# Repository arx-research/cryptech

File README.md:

# CrypTech Repos

This repository is a collection of git submodules associated with the [CrypTech](https://cryptech.is) project.

To use on a fresh repository run:
`git clone --recurse-submodules -j8 https://github.com/arx-project/cryptech.git`

Or on an already cloned repo:
`git submodule update --init --recursive`

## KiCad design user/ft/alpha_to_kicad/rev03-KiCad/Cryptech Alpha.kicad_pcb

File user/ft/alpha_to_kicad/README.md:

Work-in-progress repository with output of altium2kicad conversion
of the Cryptech Alpha rev03 board.

The conversion was done using 'convert.sh', with the Altium Designer
project files from

  https://wiki.cryptech.is/browser/hardware/cad/rev03

and the altium2kicad project from

  https://github.com/thesourcerer8/altium2kicad

Current status
--------------
NOTE: The latest stable KiCAD version as of this writing is 4.0.7 - it does
NOT include necessary support for stitching vias. Install KiCAD nightly build
to work with the Cryptech Alpha PCB.

The schematics are mostly converted. A few components do not connect with their
nets (e.g. C9 and C10 on sheet rev02_01), but maybe a manual overhaul will be
needed anyways at the end of conversion. A bigger issue is that no components
get footprints associated with them in the schema, so generating a new netlist
won't work at all. The footprints exists in some form in the PCB, so we only
need to figure out how to reference them properly in the schema.

All the copper layers convert reasonably well. The challenges are mostly
around filled polygons on the various layers. A python script (fix-pcb.py)
modifies parameters to get a fairly close result.

I'm currently looking into ensuring the drill hole sizes are right, and the
non-copper layers have been largely ignored this far.

Issues
------
Two layers (Altium Gerber files CrypTech.G1 and CrypTech.G2) have fills
that I have not been able to reproduce. I targeted not missing any copper,
accepting that the KiCAD gerber fills reach more places, so add some copper
on those layers.

Drill hole sizes have not been checked. KiCAD seems to add ~0.85 mil more
clearance around vias. This needs to be double checked but I'm hoping that
we can just tolerate that.

Importing WRL files (3D models) required some hacking of the altium2kicad
tool that I haven't been able to work on upstreaming yet. Something is still
not right here, but the board does have a fair amount of component (including
the more special ones) in KiCAD 3D view.

Another hack that has not been upstreamed is loading more of the source
files, IIRC to get all component footprints properly converted.

The KiCAD board does not pass DRC checks yet. I believe part of this is
because design rule settings aren't (fully?) imported from Altium. Need
to figure out the settings used for this project, and fix all drill sizes
I think.

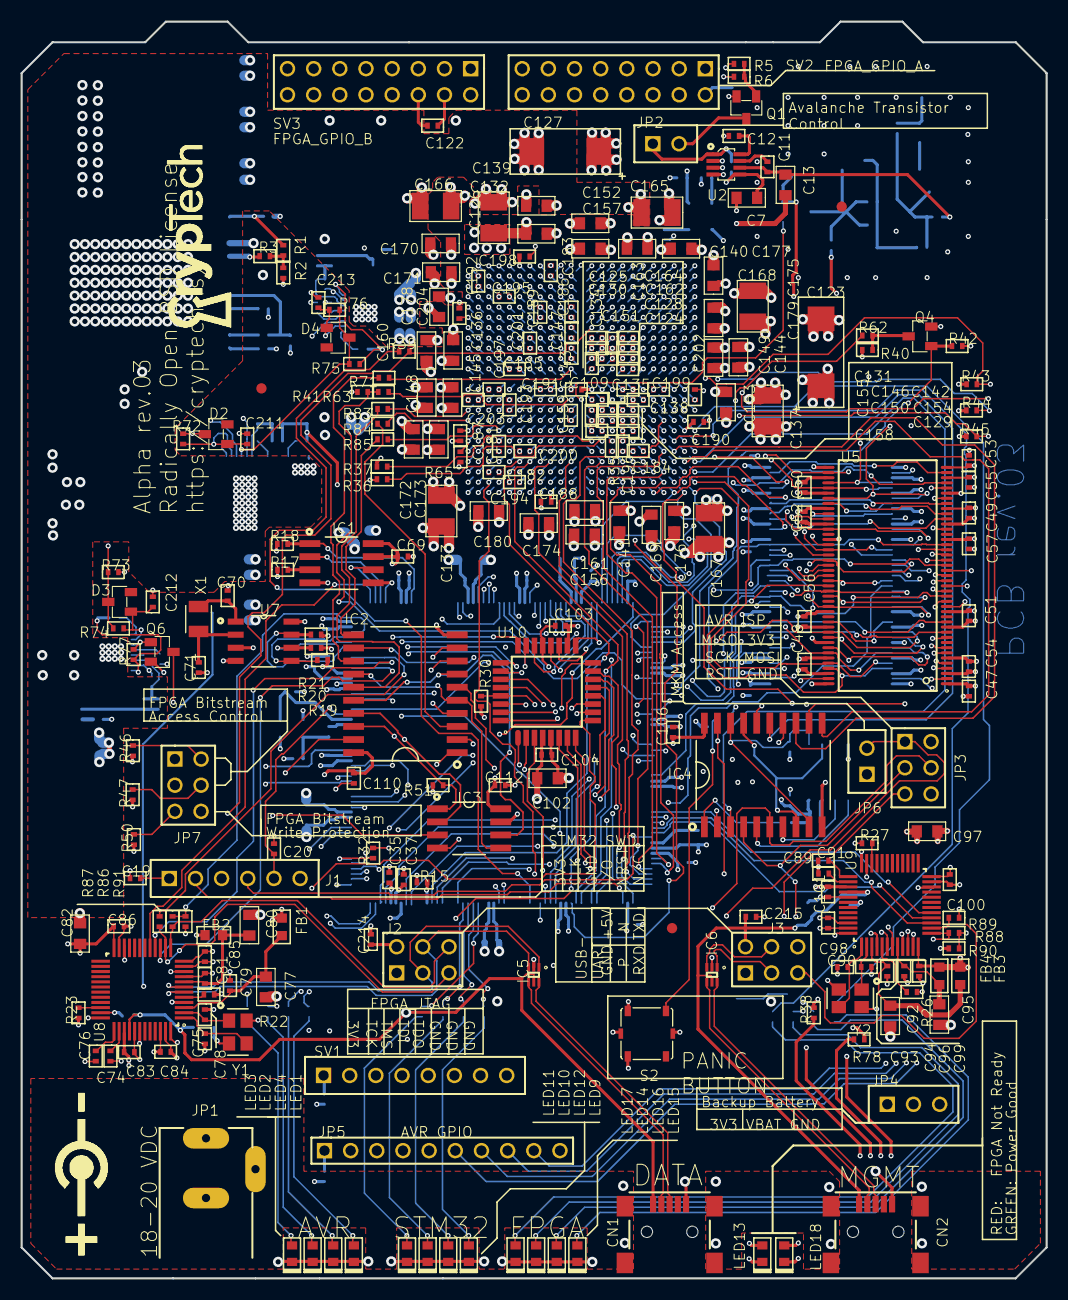
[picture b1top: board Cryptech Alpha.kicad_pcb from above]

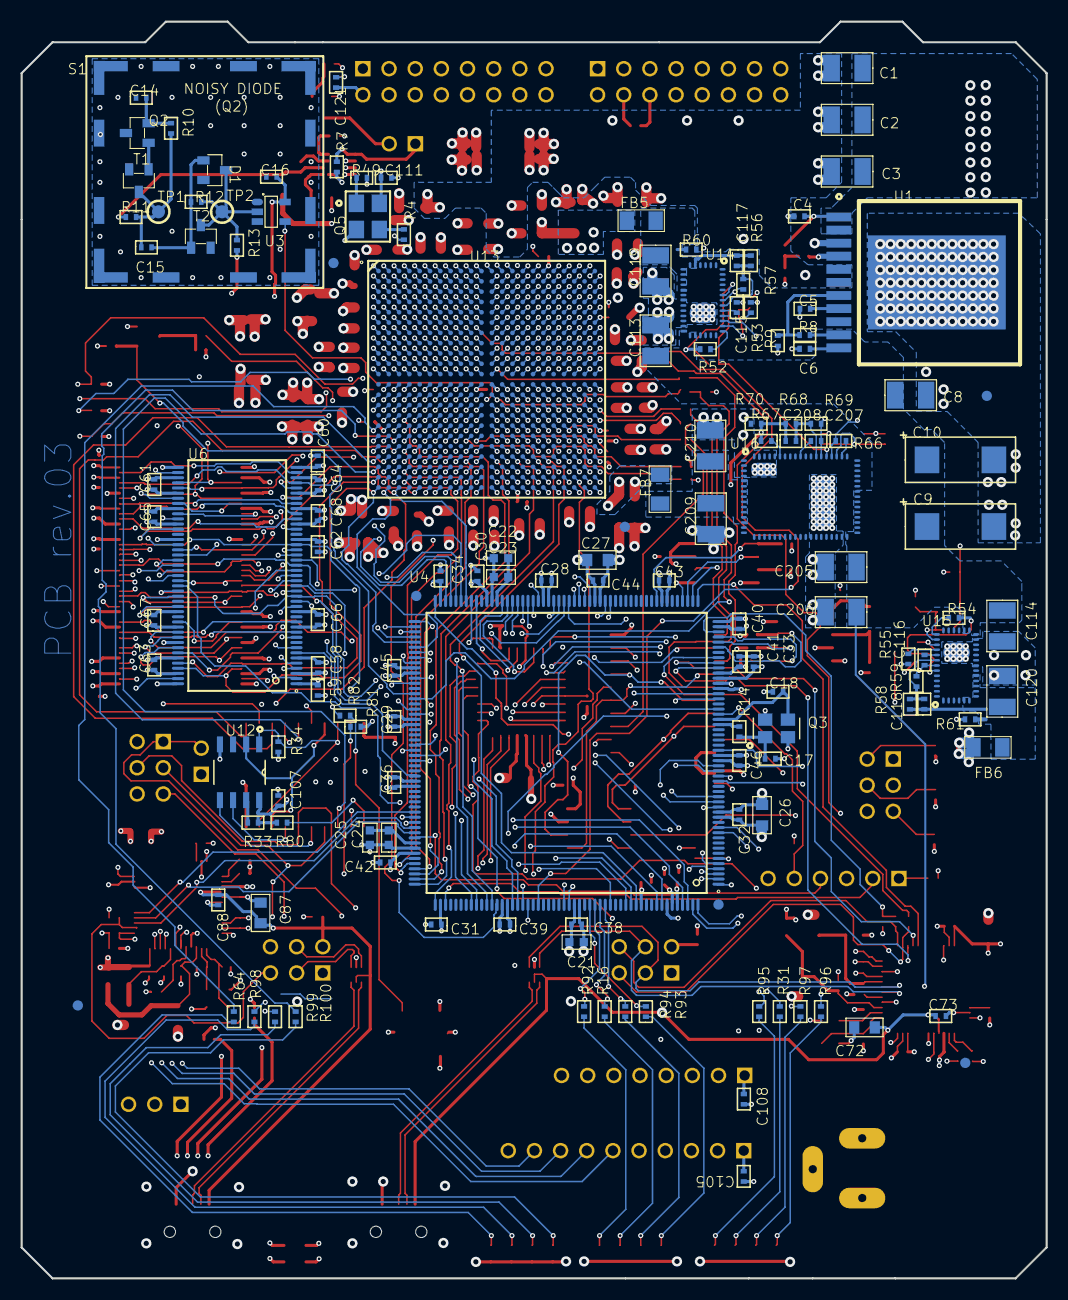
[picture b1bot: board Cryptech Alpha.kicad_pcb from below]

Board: 8 copper layers, 99.5 x 122.0 mm, 385 parts (135 on the bottom side), 302 nets.

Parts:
C1, C2, C3, C113, C114, C205, C206: 1210 CAPACITOR; C_1210
C4, C5, C6, C11, C12, C14, C15, C16, C17, C18, C19, C20, C28, C29, C30, C31, C32, C33, C34, C35, C36, C37, C38, C39, C40, C41, C42, C43, C44, C45, C46, C47, C48, C49, C50, C51, C52, C53, C54, C55, C56, C57, C58, C59, C60, C61, C62, C63, C64, C65, C66, C67, C68, C69, C70, C71, C73, C74, C75, C76, C78, C79, C81, C83, C84, C85, C86, C88, C89, C90, C91, C93, C94, C96, C98, C99, C100, C101, C103, C104, C105, C106, C107, C108, C109, C110, C111, C112, C115, C116, C117, C118, C121, C122, C124, C125, C128, C129, C130, C131, C134, C135, C138, C142, C143, C146, C147, C150, C151, C154, C155, C158, C159, C162, C163, C164, C181, C182, C183, C184, C185, C186, C187, C188, C189, C190, C191, C192, C193, C194, C195, C196, C197, C198, C199, C200, C201, C202, C203, C204, C207, C208, C211, C212, C213, C214, C215: 0402 CAPACITOR; C_0402
C7, C13: 0805 CAPACITOR X7R 25V; C_0805
C8, C119, C120, C126, C133, C137, C165, C166, C167, C168, C209, C210: 1210 CAPACITOR X5R 6.3V; C_1210
C9, C10, C123, C127: Kemet Tantalum Capacitor; C_D
C21, C22, C23, C24, C25: 0603 CAPACITOR; C_0603
C26, C27, C72, C77, C80, C82, C87, C92, C95, C97, C102, C132, C136, C139, C140, C141, C144, C145, C148, C149, C152, C153, C156, C157, C160, C161, C169, C170, C171, C172, C173, C174, C175, C176, C177, C178, C179, C180: 0805 CAPACITOR; C_0805
CN1, CN2: mini USB type B Connector; USB-MINIB
D1, D2, D3, D4: OnSemi Schottky Diode; SOT-23
FB1, FB2, FB3, FB4: Ferrite Bead 600 Ohm 500mA; L_0603
FB5, FB6, FB7: L_1206
IC1, IC3: NOR Flash; SO08
IC2, IC4: Octal BUFFER and LINE DRIVER, 3-state; SO20W
IC5, IC6: USB protective diodes; RCLAMP0502A
J1: STM32 SWD connector; PLS-6
J2, J3: 2x3 .1" header; PLD-6
JP1: Wurth Power Connector 5.5x2.1mm Barrel; 694106301002
JP2, JP6: Wurth 2pins connector (for jumper); PLS-2
JP3: PLD-6
JP4: Standard 3-pin 0.1" header. Use with straight bre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; PLS-3
JP5: Standard 10-pin 0.1" header. Use with straight br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; HDR1X10
JP7: 2x3 .1" header; PLD-6
LED1, LED9, LED15, LED18: GREEN LED; VD_0603
LED2, LED10, LED13, LED14: RED LED; VD_0603
LED3, LED11, LED17: BLUE LED; VD_0603
LED4, LED12, LED16: YELLOW LED; VD_0603
Q1, Q4, Q6: OnSemi FET; SOT-23
Q2: NPN Transistor; SOT-23
Q3: Abracon 25MHz 10pF 4-pin 3.2 x 2.5mm crystal; CRYSTAL_3.2X2.5
Q5: ASF
R1, R2, R8, R9, R10, R11, R12, R13, R22, R26, R56, R57, R58, R59, R68, R69, R72, R74, R76: 0402 Resistor 1%; R_0402
R3, R4, R5, R6, R7, R14, R15, R16, R17, R18, R19, R20, R21, R23, R27, R30, R31, R32, R33, R34, R35, R36, R37, R38, R39, R40, R41, R42, R43, R44, R45, R46, R47, R49, R50, R51, R52, R53, R54, R55, R60, R61, R62, R63, R64, R65, R66, R67, R70, R71, R73, R75, R77, R78, R80, R81, R82, R83, R84, R85, R86, R87, R88, R89, R90, R91, R92, R93, R94, R95, R96, R97, R98, R99, R100: 0402 Resistor 5%; R_0402
S1: WE-SHC Shielding cabinet; WE-SHC_36103205_NO_CREAM
S2: Tacktile switch; TACTILE_SWITCH
SV1: PIN HEADER 0.1"; PLS-8
SV2, SV3: PIN HEADER 0.1"; PLD-16
T1, T2: NPN Transistor; SOT-23
TP1, TP2: Test pad; B1,27
U1: NDY
U2: Micropower, Low Noise, 100mA LDO, Linear Regulator; TSOT-8-23
U3: Single Inverter with Schmitt-Trigger Input; SOT-23-5
U4: TSQFP50P3000X3000X160-208N
U5, U6: TSSOP50P1180X120-86N
U7: RTCC, I2C, 1K EE, 64B SRAM, 8SOIC; SOIC127P600X175-8N
U8, U9: INTERFACE, USB - UART/FIFO; LQFP-48
U10: IC, MCU, 8KB, FLASH, 20MHZ, TQFP-32; LQFP-32
U12: 64K SPI Bus Low-Power Serial SRAM,SOIC-8; SOIC127P600X175-8N
U13: Xilinx FPGA: XC7A200TFBG484; BGA484C100P22X22_2300X2300X254
U14, U15: QFN38
U16: QFN68
X1: Crystal 32.768kHz; XTAL3215
Y1, Y2: Crystal 12MHz; CRYSTAL_3.2X2.5

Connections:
3V3_BATT: C102.1, C103.1, C104.1, C106.1, C107.1, IC4.20, JP3.2, JP4.2, R30.2, R32.1, R33.1, R34.2, R80.2, R82.2, U7.3, U10.4, U10.18, U12.8
15V_LDO_ENABLE: JP2.1, R7.2, U2.1
15V_STABLE: C11.2, C13.1, R11.1, U2.6
AMPLIFIED: D1.3, R12.2, R13.1, T2.3, TP2.TP, U3.2
ARM_FPGA_CFG_CS_N: IC2.2, U4.104
ARM_FPGA_CFG_MISO: IC2.12, U4.106
ARM_FPGA_CFG_MOSI: IC2.6, U4.107
ARM_FPGA_CFG_SCLK: IC2.4, U4.105
ARM_LED1: R93.2, U4.187
ARM_LED2: R92.2, U4.188
ARM_LED3: R16.2, U4.189
ARM_LED4: R94.2, U4.190
AVR_GPIO_0: JP5.2, U10.31
AVR_GPIO_1: JP5.3, U10.32
AVR_GPIO_2: JP5.4, U10.1
AVR_GPIO_3: JP5.5, U10.2
AVR_GPIO_4: JP5.6, U10.3
AVR_GPIO_5: JP5.7, U10.6
AVR_GPIO_6: JP5.8, U10.7
AVR_GPIO_7: JP5.9, U10.8
AVR_GPIO_ARM_0: U4.97, U10.17
AVR_GPIO_ARM_1: U4.96, U10.19
AVR_GPIO_ARM_2: U4.91, U10.20
AVR_GPIO_ARM_3: U4.90, U10.22
AVR_GPIO_FPGA_0: U10.23, U13.B20
AVR_GPIO_FPGA_1: U10.24, U13.A20
AVR_GPIO_FPGA_2: U10.25, U13.A18
AVR_GPIO_FPGA_3: U10.26, U13.A19
AVR_LED1: R96.2, U10.9
AVR_LED2: R95.2, U10.10
AVR_LED3: R31.2, U10.11
AVR_LED4: R97.2, U10.12
AVR_PANIC: R82.1, S2.A2, U10.13
AVR_RESET: JP3.5, R30.1, U10.29
BOOT0: R15.2, U4.197
D1_N: CN1.D-, IC5.4
D1_P: CN1.D+, IC5.6
DIGITIZED_NOISE: U3.4, U13.W19
DM_N: CN2.D-, IC6.4
DM_P: CN2.D+, IC6.6
FMC_A0: U4.16, U5.25, U6.25, U13.Y17
FMC_A1: U4.17, U5.26, U6.26, U13.AB16
FMC_A2: U4.18, U5.27, U6.27, U13.AA16
FMC_A3: U4.22, U5.60, U6.60, U13.Y16
FMC_A4: U4.23, U5.61, U6.61, U13.AB17
FMC_A5: U4.24, U5.62, U6.62, U13.AA13
FMC_A6: U4.71, U5.63, U6.63, U13.AB13
FMC_A7: U4.74, U5.64, U6.64, U13.AA15
FMC_A8: U4.75, U5.65, U6.65, U13.AB15
FMC_A9: U4.76, U5.66, U6.66, U13.Y13
FMC_A10: U4.77, U5.24, U6.24, U13.AA14
FMC_A11: U4.78, U5.21, U6.21, U13.Y14
FMC_A12: U4.129, U5.69, U6.69, U13.AB10
FMC_A13: U4.130, U13.V2
FMC_A14: U4.131, U5.22, U6.22, U13.AB12
FMC_A15: U4.132, U5.23, U6.23, U13.AB8
FMC_A16: U4.111, U13.AA9
FMC_A17: U4.112, U13.AA8
FMC_A18: U4.113, U13.Y7
FMC_A19: U4.2, U13.AB21
FMC_A20: U4.3, U13.AB22
FMC_A21: U4.4, U13.AB20
FMC_A22: U4.5, U13.Y21
FMC_A23: U4.1, U13.Y22
FMC_A24: U4.182, U13.AB18
FMC_A25: U4.183, U13.AA19
FMC_CLK: U4.167, U13.W11
FMC_D0: U4.116, U5.2, U6.2, U13.AB7
FMC_D1: U4.117, U5.4, U6.4, U13.AB6
FMC_D2: U4.164, U5.5, U6.5, U13.U1
FMC_D3: U4.165, U5.7, U6.7, U13.U2
FMC_D4: U4.79, U5.8, U6.8, U13.AB11
FMC_D5: U4.80, U5.10, U6.10, U13.AA11
FMC_D6: U4.81, U5.11, U6.11, U13.Y11
FMC_D7: U4.84, U5.13, U6.13, U13.Y12
FMC_D8: U4.85, U5.74, U6.74, U13.Y18
FMC_D9: U4.86, U5.76, U6.76, U13.AA21
FMC_D10: U4.87, U5.77, U6.77, U13.W20
FMC_D11: U4.88, U5.79, U6.79, U13.N15
FMC_D12: U4.89, U5.80, U6.80, U13.U20
FMC_D13: U4.108, U5.82, U6.82, U13.AA1
FMC_D14: U4.109, U5.83, U6.83, U13.AB1
FMC_D15: U4.110, U5.85, U6.85, U13.AB2
FMC_D16: U4.98, U5.31, U6.31, U13.AB3
FMC_D17: U4.99, U5.33, U6.33, U13.Y3
FMC_D18: U4.100, U5.34, U6.34, U13.AA3
FMC_D19: U4.101, U5.36, U6.36, U13.AA5
FMC_D20: U4.102, U5.37, U6.37, U13.AB5
FMC_D21: U4.151, U5.39, U6.39, U13.Y4
FMC_D22: U4.152, U5.40, U6.40, U13.AA4
FMC_D23: U4.153, U5.42, U6.42, U13.V4
FMC_D24: U4.154, U5.45, U6.45, U13.W10
FMC_D25: U4.155, U5.47, U6.47, U13.R4
FMC_D26: U4.156, U5.48, U6.48, U13.W12
FMC_D27: U4.157, U5.50, U6.50, U13.W14
FMC_D28: U4.207, U5.51, U6.51, U13.V20
FMC_D29: U4.208, U5.53, U6.53, U13.V18
FMC_D30: U4.11, U5.54, U6.54, U13.R21
FMC_D31: U4.12, U5.56, U6.56, U13.P21
FMC_NBL0: U4.200, U5.16, U6.16
FMC_NBL1: U4.201, U5.71, U6.71
FMC_NBL2: U4.205, U5.28, U6.28
FMC_NBL3: U4.206, U5.59, U6.59
FMC_NE1: U4.173, U13.V5
FMC_NL: U4.196, U13.W17
FMC_NOE: U4.168, U13.W16
FMC_NWAIT: U4.172, U13.Y6
FMC_NWE: U4.169, U13.AA6
FMC_SDCKE0: U4.38, U5.67
FMC_SDCKE1: U4.194, U6.67
FMC_SDCLK: U4.135, U5.68, U6.68
FMC_SDNCAS: U4.191, U5.18, U6.18
FMC_SDNE0: U4.37, U5.20
FMC_SDNE1: U4.195, U6.20
FMC_SDNRAS: U4.70, U5.19, U6.19
FMC_SDNWE: U4.35, U5.17, U6.17
FPGA_CFG_CS_N: IC2.11, R85.1
FPGA_CFG_CS_N1: R85.2, U13.T19
FPGA_CFG_CTRL_ARM_ENA: JP7.1, U4.27
FPGA_CFG_CTRL_FPGA_DIS: JP7.3, U4.21
FPGA_CFG_MISO: IC2.3, R84.1
FPGA_CFG_MISO1: R84.2, U13.R22
FPGA_CFG_MOSI: IC2.15, R83.1
FPGA_CFG_MOSI1: R83.2, U13.P22
FPGA_CFG_SCLK: IC2.13, R71.1
FPGA_CFG_SCLK1: R71.2, U13.L12
FPGA_DONE: R39.1, U4.177
FPGA_DONE_INT: LED13.2, R39.2, U13.G11
FPGA_ENTROPY_DISABLE: R5.1, U13.B18
FPGA_GCLK: R4.1, U13.D17
FPGA_GPIO_A_0: SV2.7, U13.E14
FPGA_GPIO_A_1: SV2.8, U13.E13
FPGA_GPIO_A_2: SV2.9, U13.A13
FPGA_GPIO_A_3: SV2.10, U13.A14
FPGA_GPIO_A_4: SV2.13, U13.C13
FPGA_GPIO_A_5: SV2.14, U13.B13
FPGA_GPIO_A_6: SV2.15, U13.A15
FPGA_GPIO_A_7: SV2.16, U13.B15
FPGA_GPIO_B_0: SV3.7, U13.A16
FPGA_GPIO_B_1: SV3.8, U13.C15
FPGA_GPIO_B_2: SV3.9, U13.B16
FPGA_GPIO_B_3: SV3.10, U13.D14
FPGA_GPIO_B_4: SV3.13, U13.C18
FPGA_GPIO_B_5: SV3.14, U13.A21
FPGA_GPIO_B_6: SV3.15, U13.C20
FPGA_GPIO_B_7: SV3.16, U13.C22
FPGA_GPIO_LED_0: R100.2, U13.U3
FPGA_GPIO_LED_1: R64.2, U13.T1
FPGA_GPIO_LED_2: R98.2, U13.W22
FPGA_GPIO_LED_3: R99.2, U13.AA20
FPGA_INIT_B: Q4.1, R42.2, U4.119
FPGA_INIT_B_INT: Q4.3, R40.1, R62.1
FPGA_INIT_B_INT1: R62.2, U13.U12
FPGA_IRQ_N_0: U4.122, U13.F14
FPGA_IRQ_N_1: U4.123, U13.F16
FPGA_IRQ_N_2: U4.174, U13.E17
FPGA_IRQ_N_3: U4.175, U13.C14
FPGA_JTAG_TCK: R45.1, SV1.2, U13.V12
FPGA_JTAG_TDI: R43.1, SV1.4, U13.R13
FPGA_JTAG_TDO: SV1.5, U13.U13
FPGA_JTAG_TMS: R44.1, SV1.3, U13.T13
FPGA_M0: R37.1, U13.U11
FPGA_M1: R36.2, U13.U10
FPGA_M2: R35.2, U13.U9
FPGA_PROGRAM_B: R41.1, R63.1, U4.120
FPGA_PROGRAM_B1: R63.2, U13.N12
FPGA_PROM_CS_N: IC2.9, IC2.18, IC3.1, R51.1
FPGA_PROM_MISO: IC2.8, IC2.17, IC3.2
FPGA_PROM_MOSI: IC2.5, IC2.14, IC3.5
FPGA_PROM_SCLK: IC2.7, IC2.16, IC3.6
FPGA_PROM_W_N: IC3.3, JP7.5, R50.2
FPGA_VCCAUX_1V8: C109.1, C126.1, C132.1, C136.1, C139.1, C143.1, C147.1, C151.1, C155.1, C159.1, FB5.2, U13.H12, U13.K10, U13.K12, U13.M12, U13.P12, U13.R11
FPGA_VCCINT_1V0: C123.1, C124.1, C125.1, C127.1, C128.1, C129.1, C130.1, C131.1, C133.1, C134.1, C135.1, C137.1, C138.1, C140.1, C141.1, C142.1, C144.1, C145.1, C146.1, C148.1, C149.1, C150.1, C152.1, C153.1, C154.1, C156.1, C157.1, C158.1, C160.1, C161.1, C162.1, C163.1, C164.1, FB7.2, U13.H8, U13.H10, U13.J7, U13.J9, U13.J11, U13.K8, U13.L7, U13.L11, U13.M8, U13.N7, U13.N11, U13.P8, U13.P10, U13.R7, U13.R9, U13.T8, U13.T10
FT_CTS: U4.44, U8.16
FT_DTR: U4.53, U8.17
FT_MGMT_CTS: U4.146, U9.16
FT_MGMT_DTR: U4.142, U9.17
FT_MGMT_RTS: U4.145, U9.15
FT_MGMT_RXD: R89.1, U4.143
FT_MGMT_RXD1: J3.5, R89.2, U9.14
FT_MGMT_TXD: R88.1, R90.2, U4.144
FT_MGMT_TXD1: J3.6, R88.2, U9.13
FT_MGMT_VCC3V3: C97.1, C98.1, C99.1, C100.1, C101.1, FB3.1, FB4.1, R27.2, U9.12, U9.24, U9.39, U9.46
FT_MGMT_VPHY: C92.1, C94.1, FB3.2, U9.3
FT_MGMT_VPLL: C95.1, C96.1, FB4.2, U9.8
FT_MGMT_VREGIN: C87.1, C88.1, C215.1, CN2.VBUS, IC6.5, J3.2, U9.40
FT_REF: R22.1, U8.5
FT_REF1: R26.1, U9.5
FT_RESET: R23.1, U8.34
FT_RESET1: R27.1, U9.34
FT_RTS: U4.43, U8.15
FT_RXD: R87.1, U4.45
FT_RXD1: J2.5, R87.2, U8.14
FT_TXD: R86.1, R91.2, U4.50
FT_TXD1: J2.6, R86.2, U8.13
FT_VCC3V3: C82.1, C83.1, C84.1, C85.1, C86.1, FB1.1, FB2.1, R23.2, U8.12, U8.24, U8.39, U8.46
FT_VCCA: C76.1, U8.37
FT_VCCA1: C91.1, U9.37
FT_VCCORE: C74.1, U8.38
FT_VCCORE1: C89.1, U9.38
FT_VPHY: C77.1, C79.1, FB1.2, U8.3
FT_VPLL: C80.1, C81.1, FB2.2, U8.8
FT_VREGIN: C72.1, C73.1, C214.1, CN1.VBUS, IC5.5, J2.2, U8.40
GND: C1.2, C2.2, C3.2, C4.2, C5.2, C6.2, C7.2, C8.2, C9.2, C10.2, C12.1, C13.2, C14.1, C16.1, C17.1, C18.1, C19.2, C20.2, C21.2, C22.1, C23.1, C24.1, C25.1, C26.2, C27.2, C28.2, C29.2, C30.2, C31.2, C32.2, C33.2, C34.2, C35.2, C36.2, C37.2, C38.2, C39.2, C40.2, C41.2, C42.2, C43.2, C44.2, C45.2, C46.2, C47.2, C48.2, C49.2, C50.2, C51.2, C52.2, C53.2, C54.2, C55.2, C56.2, C57.2, C58.2, C59.2, C60.2, C61.2, C62.2, C63.2, C64.2, C65.2, C66.2, C67.2, C68.2, C69.2, C70.1, C71.1, C72.2, C73.2, C74.2, C75.1, C76.2, C77.2, C78.1, C79.2, C80.2, C81.2, C82.2, C83.2, C84.2, C85.2, C86.2, C87.2, C88.2, C89.2, C90.1, C91.2, C92.2, C93.1, C94.2, C95.2, C96.2, C97.2, C98.2, C99.2, C100.2, C101.2, C102.2, C103.2, C104.2, C105.2, C106.2, C107.2, C108.2, C109.2, C110.2, C111.2, C112.2, C113.2, C114.2, C115.2, C116.2, C119.2, C120.2, C121.2, C122.2, C123.2, C124.2, C125.2, C126.2, C127.2, C128.2, C129.2, C130.2, C131.2, C132.2, C133.2, C134.2, C135.2, C136.2, C137.2, C138.2, C139.2, C140.2, C141.2, C142.2, C143.2, C144.2, C145.2, C146.2, C147.2, C148.2, C149.2, C150.2, C151.2, C152.2, C153.2, C154.2, C155.2, C156.2, C157.2, C158.2, C159.2, C160.2, C161.2, C162.2, C163.2, C164.2, C165.2, C166.2, C167.2, C168.2, C169.2, C170.2, C171.2, C172.2, C173.2, C174.2, C175.2, C176.2, C177.2, C178.2, C179.2, C180.2, C181.2, C182.2, C183.2, C184.2, C185.2, C186.2, C187.2, C188.2, C189.2, C190.2, C191.2, C192.2, C193.2, C194.2, C195.2, C196.2, C197.2, C198.2, C199.2, C200.2, C201.2, C202.2, C203.2, C204.2, C205.2, C206.2, C207.2, C209.2, C210.2, C211.2, C212.2, C213.2, C214.2, C215.2, CN1.GND, CN2.GND, IC1.4, IC2.10, IC3.4, IC4.10, IC5.2, IC6.2, J1.3, J2.1, J3.1, JP1.2, JP1.3, JP3.6, JP4.3, JP5.10, JP6.1, LED1.2, LED2.2, LED3.2, LED4.2, LED9.2, LED10.2, LED11.2, LED12.2, LED14.2, LED15.2, LED16.2, LED17.2, Q1.2, Q3.2, Q3.4, Q4.2, Q5.2, Q6.2, R2.1, R6.2, R9.1, R15.1, R22.2, R26.2, R35.1, R36.1, R42.1, R47.2, R50.1, R53.1, R55.1, R57.1, R59.1, R60.1, R61.1, R69.1, R70.1, R81.2, S1.1, S2.B1, S2.B2, S2.G1, S2.G2, SV1.6, SV1.7, SV1.8, SV2.5, SV2.6, SV2.11, SV2.12, SV3.5, SV3.6, SV3.11, SV3.12, T1.2, T2.2, U1.3, U1.5, U1.6, U1.TP1, U2.2, U2.3, U2.4, U3.3, U4.14, U4.25, U4.40, U4.51, U4.60, U4.72, U4.82, U4.93, U4.114, U4.125, U4.136, U4.149, U4.170, U4.184, U4.202, U5.6, U5.12, U5.32, U5.38, U5.44, U5.46, U5.52, U5.58, U5.72, U5.78, U5.84, U5.86, U6.6, U6.12, U6.32, U6.38, U6.44, U6.46, U6.52, U6.58, U6.72, U6.78, U6.84, U6.86, U7.4, U8.4, U8.9, U8.10, U8.11, U8.22, U8.23, U8.35, U8.36, U8.41, U8.42, U8.47, U8.48, U9.4, U9.9, U9.10, U9.11, U9.22, U9.23, U9.35, U9.36, U9.41, U9.42, U9.47, U9.48, U10.5, U10.21, U12.4, U13.A2, U13.A3, U13.A5, U13.A7, U13.A9, U13.A11, U13.A12, U13.A22, U13.AA2, U13.AA12, U13.AA22, U13.AB9, U13.AB19, U13.B3, U13.B12, U13.B19, U13.C3, U13.C6, U13.C10, U13.C12, U13.C16, U13.D3, U13.D4, U13.D8, U13.D12, U13.D13, U13.E4, U13.E5, U13.E7, U13.E9, U13.E11, U13.E12, U13.E20, U13.F5, U13.F11, U13.F17, U13.G5, U13.G6, U13.G7, U13.G8, U13.G9, U13.G10, U13.G12, U13.G14, U13.H1, U13.H7, U13.H9, U13.H11, U13.H21, U13.J8, U13.J10, U13.J12, U13.J18, U13.K5, U13.K7, U13.K9, U13.K11, U13.K15, U13.L2, U13.L8, U13.L9, U13.L22, U13.M7, U13.M10, U13.M11, U13.M19, U13.N6, U13.N8, U13.N9, U13.N10, U13.N16, U13.P3, U13.P7, U13.P9, U13.P11, U13.P13, U13.R8, U13.R10, U13.R12, U13.R20, U13.T7, U13.T9, U13.T11, U13.T17, U13.U4, U13.U14, U13.V1, U13.V11, U13.V21, U13.W8, U13.W18, U13.Y5, U13.Y15, U14.13, U14.14, U14.15, U14.16, U14.17, U14.18, U14.32, U14.PAD39, U15.13, U15.14, U15.15, U15.16, U15.17, U15.18, U15.32, U15.PAD39, U16.1, U16.2, U16.3, U16.4, U16.27, U16.28, U16.29, U16.30, U16.31, U16.32, U16.33, U16.55, U16.64, U16.65, U16.66, U16.67, U16.68, U16.PAD69, U16.PAD70, Y1.2, Y1.4, Y2.2, Y2.4
KSM_PROM_CS_N: IC1.1, R18.2, U4.61
KSM_PROM_MISO: IC1.2, U4.55
KSM_PROM_MOSI: IC1.5, U4.56
KSM_PROM_SCLK: IC1.6, U4.54
MKM_AVR_CS_N: IC4.2, U10.14
MKM_AVR_MISO: IC4.12, JP3.1, JP6.2, U10.28
MKM_AVR_MOSI: IC4.6, JP3.4, U10.27
MKM_AVR_SCK: IC4.4, JP3.3, U10.30
MKM_CONTROL_AVR_ENA: IC4.1, R80.1, U10.15
MKM_CONTROL_FPGA_DIS: IC4.19, R81.1, U10.16
MKM_CS_N: IC4.9, IC4.18, R34.1, U12.1
MKM_FPGA_CS_N: IC4.11, U13.W2
MKM_FPGA_MISO: IC4.3, U13.Y1
MKM_FPGA_MOSI: IC4.15, U13.W1
MKM_FPGA_SCK: IC4.13, U13.V3
MKM_MISO: IC4.8, IC4.17, U12.2
MKM_MOSI: IC4.5, IC4.14, U12.5
MKM_SCK: IC4.7, IC4.16, U12.6
NOISE_IN: C14.2, Q2.2, R10.2
NOISE_OUT: Q2.1, T1.1
NRST: C20.1, J1.5, U4.34
NetC5_1: C5.1, U1.8
NetC11_1: C11.1, U2.7
NetC12_2: C12.2, U2.8
NetC15_2: C15.2, D1.1, R12.1, T2.1
NetC17_2: C17.2, Q3.1, R14.2
NetC70_2: C70.2, U7.1, X1.P$1
NetC71_2: C71.2, U7.2, X1.P$2
NetC75_2: C75.2, U8.1, Y1.3
NetC78_2: C78.2, U8.2, Y1.1
NetC90_2: C90.2, U9.1, Y2.3
NetC93_2: C93.2, U9.2, Y2.1
NetC115_1: C115.1, U14.30
NetC116_1: C116.1, U15.30
NetC117_1: C117.1, C119.1, FB5.1, R56.2, R60.2, U14.5, U14.6, U14.7, U14.8, U14.9, U14.10, U14.11
NetC117_2: C117.2, R56.1, R57.2, U14.31
NetC118_1: C118.1, C120.1, FB6.1, R58.2, R61.2, U15.5, U15.6, U15.7, U15.8, U15.9, U15.10, U15.11
NetC118_2: C118.2, R58.1, R59.2, U15.31
NetC207_1: C207.1, U16.59
NetC208_1: C208.1, C209.1, C210.1, FB7.1, R67.2, R68.2, R70.2, U16.5, U16.6, U16.7, U16.8, U16.9, U16.10, U16.11, U16.12, U16.13
NetC208_2: C208.2, R68.1, R69.2, U16.56
NetIC1_3: IC1.3, R17.2
NetJP2_2: JP2.2, Q1.3
NetLED1_1: LED1.1, R92.1
NetLED2_1: LED2.1, R94.1
NetLED3_1: LED3.1, R93.1
NetLED4_1: LED4.1, R16.1
NetLED9_1: LED9.1, R95.1
NetLED10_1: LED10.1, R97.1
NetLED11_1: LED11.1, R96.1
NetLED12_1: LED12.1, R31.1
NetLED13_1: LED13.1, R38.1
NetLED14_1: LED14.1, R99.1
NetLED15_1: LED15.1, R64.1
NetLED16_1: LED16.1, R98.1
NetLED17_1: LED17.1, R100.1
NetLED18_1: LED18.1, R78.1
NetLED18_2: LED18.2, Q6.3
NetQ1_1: Q1.1, R5.2, R6.1
NetQ5_1: Q5.1, R49.1
NetQ5_3: Q5.3, R4.2
NetR1_1: R1.1, R2.2, R3.1
NetR3_2: R3.2, U1.4
NetR8_1: R8.1, R9.2, U1.7
NetR32_2: R32.2, U4.6
NetR33_2: R33.2, U12.7
NetR52_1: R52.1, U14.26
NetR53_2: R53.2, U14.29
NetR54_1: R54.1, U15.26
NetR55_2: R55.2, U15.29
NetR65_1: R65.1, U13.U22
NetR66_1: R66.1, U16.51
NetR67_1: R67.1, U16.63
OSC_IN: R14.1, U4.32
OSC_OUT: C18.2, Q3.3, U4.33
POK_VCCAUX: D3.3, R73.1, R74.1, U14.28
POK_VCCINT: D4.3, R75.1, R76.1, U16.54
POK_VCCO: Q6.1, R77.1, U15.28
PWR_18V: C1.1, C2.1, C3.1, C4.1, C7.1, JP1.1, R1.2, R7.1, U1.1, U1.2, U2.5
PWR_ENA_VCCAUX: C213.1, D4.1, R76.2, U14.27
PWR_ENA_VCCINT: C211.1, D2.1, R72.2, U16.52
PWR_ENA_VCCO: C212.1, D3.1, R74.2, U15.27
RAW_NOISE: C15.1, R10.1, R11.2, T1.3, TP1.TP
RTC_MFP: R21.2, U4.47, U7.7
RTC_SCL: R20.2, U4.48, U7.6
RTC_SDA: R19.2, U4.49, U7.5
SPI_A_TRISTATE: IC2.1, JP7.2, R46.1
SPI_B_TRISTATE: IC2.19, JP7.4, R47.1
SWDCLK: J1.2, U4.159
SWDIO: J1.4, U4.147
USB_MGMT_N: IC6.3, J3.4, U9.6
USB_MGMT_P: IC6.1, J3.3, U9.7
USB_N: IC5.3, J2.4, U8.6
USB_P: IC5.1, J2.3, U8.7
VCAP1: C22.2, C23.2, U4.92
VCAP2: C24.2, C25.2, U4.148
VCCO_3V3: C16.2, C19.1, C21.1, C26.1, C27.1, C28.1, C29.1, C30.1, C31.1, C32.1, C33.1, C34.1, C35.1, C36.1, C37.1, C38.1, C39.1, C40.1, C41.1, C42.1, C43.1, C44.1, C45.1, C46.1, C47.1, C48.1, C49.1, C50.1, C51.1, C52.1, C53.1, C54.1, C55.1, C56.1, C57.1, C58.1, C59.1, C60.1, C61.1, C62.1, C63.1, C64.1, C65.1, C66.1, C67.1, C68.1, C69.1, C105.1, C108.1, C110.1, C111.1, C112.1, C121.1, C122.1, C165.1, C166.1, C167.1, C168.1, C169.1, C170.1, C171.1, C172.1, C173.1, C174.1, C175.1, C176.1, C177.1, C178.1, C179.1, C180.1, C181.1, C182.1, C183.1, C184.1, C185.1, C186.1, C187.1, C188.1, C189.1, C190.1, C191.1, C192.1, C193.1, C194.1, C195.1, C196.1, C197.1, C198.1, C199.1, C200.1, C201.1, C202.1, C203.1, C204.1, FB6.2, IC1.7, IC1.8, IC2.20, IC3.7, IC3.8, J1.1, JP4.1, JP5.1, JP7.6, Q5.4, R13.2, R17.1, R18.1, R19.1, R20.1, R21.1, R37.2, R38.2, R40.2, R41.2, R43.2, R44.2, R45.2, R46.2, R49.2, R51.2, R65.2, R90.1, R91.1, SV1.1, SV2.1, SV2.2, SV2.3, SV2.4, SV3.1, SV3.2, SV3.3, SV3.4, U3.5, U4.15, U4.26, U4.39, U4.41, U4.42, U4.52, U4.59, U4.73, U4.83, U4.94, U4.103, U4.115, U4.124, U4.137, U4.150, U4.158, U4.171, U4.185, U4.203, U4.204, U5.1, U5.3, U5.15, U5.29, U5.35, U5.41, U5.43, U5.49, U5.55, U5.75, U5.81, U6.1, U6.3, U6.15, U6.29, U6.35, U6.41, U6.43, U6.49, U6.55, U6.75, U6.81, U7.8, U13.A17, U13.AA7, U13.AA17, U13.AB4, U13.AB14, U13.B14, U13.C1, U13.C21, U13.D18, U13.E15, U13.F2, U13.F12, U13.F22, U13.G19, U13.H6, U13.H16, U13.J3, U13.J13, U13.K20, U13.L17, U13.M4, U13.M14, U13.N1, U13.N21, U13.P18, U13.R5, U13.R15, U13.T2, U13.T12, U13.T22, U13.U8, U13.U19, U13.V6, U13.V16, U13.W3, U13.W13, U13.Y10, U13.Y20
VCC_5V0: C6.1, C8.1, C9.1, C10.1, C113.1, C114.1, C205.1, C206.1, D2.3, R8.2, R52.2, R54.2, R66.2, R72.1, R73.2, R75.2, R77.2, R78.2, U1.10, U1.11, U14.19, U14.20, U14.21, U14.33, U15.19, U15.20, U15.21, U15.33, U16.34, U16.35, U16.36, U16.37, U16.38, U16.39, U16.40, U16.41, U16.42, U16.43, U16.53

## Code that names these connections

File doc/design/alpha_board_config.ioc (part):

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Mcu.Name=STM32F439B(G-I)Tx
Mcu.Package=LQFP208
Mcu.UserName=STM32F439BITx
PA10.Mode=Asynchronous
PA10.Signal=USART1_RX
PA2.Mode=Asynchronous
PA2.Signal=USART2_TX
PA3.Mode=Asynchronous
PA3.Signal=USART2_RX
PA5.Mode=Full_Duplex_Master
PA5.Signal=SPI1_SCK
PA6.Mode=Full_Duplex_Master
PA6.Signal=SPI1_MISO
PA7.Mode=Full_Duplex_Master
PA7.Signal=SPI1_MOSI
PA9.Mode=Asynchronous
PA9.Signal=USART1_TX
PB10.Mode=Asynchronous
PB10.Signal=USART3_TX
PB11.Mode=Asynchronous
PB11.Signal=USART3_RX
PB13.Mode=Full_Duplex_Master
PB13.Signal=SPI2_SCK
PB6.Mode=I2C
PB6.Signal=I2C1_SCL
PB7.Mode=I2C
PB7.Signal=I2C1_SDA
PC0.Signal=FMC_SDNWE
PC10.Mode=mmc_4_bits_Wide_bus
PC10.Signal=SDIO_D2
PC11.Mode=mmc_4_bits_Wide_bus
PC11.Signal=SDIO_D3
PC12.Mode=mmc_4_bits_Wide_bus
PC12.Signal=SDIO_CK
PC2.Mode=Full_Duplex_Master
PC2.Signal=SPI2_MISO
PC3.Mode=Full_Duplex_Master
PC3.Signal=SPI2_MOSI
PC8.Mode=mmc_4_bits_Wide_bus
PC8.Signal=SDIO_D0
PC9.Mode=mmc_4_bits_Wide_bus
PC9.Signal=SDIO_D1
PD0.Signal=FMC_D2_DA2
PD1.Signal=FMC_D3_DA3
PD10.Signal=FMC_D15_DA15
PD11.Signal=FMC_A16_CLE
PD12.Signal=FMC_A17_ALE
PD13.Signal=FMC_A18
PD14.Signal=FMC_D0_DA0
PD15.Signal=FMC_D1_DA1
PD2.Mode=mmc_4_bits_Wide_bus
PD2.Signal=SDIO_CMD
PD4.Signal=FMC_NOE
PD5.Signal=FMC_NWE
PD7.Mode=NorPsramChipSelect1_1
PD7.Signal=FMC_NE1
PD8.Signal=FMC_D13_DA13
PD9.Signal=FMC_D14_DA14
PE0.Signal=FMC_NBL0
PE1.Signal=FMC_NBL1
PE10.Signal=FMC_D7_DA7
PE11.Signal=FMC_D8_DA8
PE12.Signal=FMC_D9_DA9
PE13.Signal=FMC_D10_DA10
PE14.Signal=FMC_D11_DA11
PE15.Signal=FMC_D12_DA12
PE2.Signal=FMC_A23
PE3.Signal=FMC_A19
PE4.Signal=FMC_A20
PE5.Signal=FMC_A21
PE6.Signal=FMC_A22
PE7.Signal=FMC_D4_DA4
PE8.Signal=FMC_D5_DA5
PE9.Signal=FMC_D6_DA6
PF0.Signal=FMC_A0
PF1.Signal=FMC_A1
PF11.Signal=FMC_SDNRAS
PF12.Signal=FMC_A6
PF13.Signal=FMC_A7
PF14.Signal=FMC_A8
PF15.Signal=FMC_A9
PF2.Signal=FMC_A2
PF3.Signal=FMC_A3
PF4.Signal=FMC_A4
PF5.Signal=FMC_A5
PG0.Signal=FMC_A10
PG1.Signal=FMC_A11
PG13.Signal=FMC_A24
PG14.Signal=FMC_A25
PG15.Signal=FMC_SDNCAS
PG2.Signal=FMC_A12
PG3.Signal=FMC_A13
PG4.Signal=FMC_A14_BA0
PG5.Signal=FMC_A15_BA1
PG8.Signal=FMC_SDCLK
PH10.Signal=FMC_D18
PH11.Signal=FMC_D19
PH12.Signal=FMC_D20
PH13.Signal=FMC_D21
PH14.Signal=FMC_D22
PH15.Signal=FMC_D23
PH2.Mode=SdramChipSelect1_1
PH2.Signal=FMC_SDCKE0
PH3.Mode=SdramChipSelect1_1
PH3.Signal=FMC_SDNE0
PH6.Mode=SdramChipSelect2_2
PH6.Signal=FMC_SDNE1
PH7.Mode=SdramChipSelect2_2
PH7.Signal=FMC_SDCKE1
PH8.Signal=FMC_D16
PH9.Signal=FMC_D17
PI0.Signal=FMC_D24
PI1.Signal=FMC_D25
PI10.Signal=FMC_D31
PI2.Signal=FMC_D26
PI3.Signal=FMC_D27
PI4.Signal=FMC_NBL2
PI5.Signal=FMC_NBL3
PI6.Signal=FMC_D28
PI7.Signal=FMC_D29
PI9.Signal=FMC_D30
RCC.HSE_VALUE=25000000
RCC.SYSCLKFreq_VALUE=16000000

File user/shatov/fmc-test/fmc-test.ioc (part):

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Mcu.Name=STM32F429B(E-G-I)Tx
Mcu.Package=LQFP208
Mcu.UserName=STM32F429BITx
PA13.Mode=Serial-Wire
PA13.Signal=SYS_JTMS-SWDIO
PA14.Mode=Serial-Wire
PA14.Signal=SYS_JTCK-SWCLK
PB7.Signal=FMC_NL
PD0.Signal=FMC_D2_DA2
PD1.Signal=FMC_D3_DA3
PD10.Signal=FMC_D15_DA15
PD11.Signal=FMC_A16_CLE
PD12.Signal=FMC_A17_ALE
PD13.Signal=FMC_A18
PD14.Signal=FMC_D0_DA0
PD15.Signal=FMC_D1_DA1
PD3.Signal=FMC_CLK
PD4.Signal=FMC_NOE
PD5.Signal=FMC_NWE
PD6.GPIOParameters=GPIO_PuPd,GPIO_Label,GPIO_Mode
PD6.GPIO_Label=FMC_NWAIT
PD6.GPIO_Mode=GPIO_MODE_INPUT
PD6.GPIO_PuPd=GPIO_NOPULL
PD6.Signal=GPIO_Input
PD7.Mode=NorPsramChipSelect1_1
PD7.Signal=FMC_NE1
PD8.Signal=FMC_D13_DA13
PD9.Signal=FMC_D14_DA14
PE10.Signal=FMC_D7_DA7
PE11.Signal=FMC_D8_DA8
PE12.Signal=FMC_D9_DA9
PE13.Signal=FMC_D10_DA10
PE14.Signal=FMC_D11_DA11
PE15.Signal=FMC_D12_DA12
PE3.Signal=FMC_A19
PE4.Signal=FMC_A20
PE5.Signal=FMC_A21
PE7.Signal=FMC_D4_DA4
PE8.Signal=FMC_D5_DA5
PE9.Signal=FMC_D6_DA6
PF0.Signal=FMC_A0
PF1.Signal=FMC_A1
PF12.Signal=FMC_A6
PF13.Signal=FMC_A7
PF14.Signal=FMC_A8
PF15.Signal=FMC_A9
PF2.Signal=FMC_A2
PF3.Signal=FMC_A3
PF4.Signal=FMC_A4
PF5.Signal=FMC_A5
PG0.Signal=FMC_A10
PG1.Signal=FMC_A11
PG2.Signal=FMC_A12
PG3.Signal=FMC_A13
PG4.Signal=FMC_A14_BA0
PG5.Signal=FMC_A15_BA1
PH10.Signal=FMC_D18
PH11.Signal=FMC_D19
PH12.Signal=FMC_D20
PH13.Signal=FMC_D21
PH14.Signal=FMC_D22
PH15.Signal=FMC_D23
PH8.Signal=FMC_D16
PH9.Signal=FMC_D17
PI0.Signal=FMC_D24
PI1.Signal=FMC_D25
PI10.Signal=FMC_D31
PI2.Signal=FMC_D26
PI3.Signal=FMC_D27
PI6.Signal=FMC_D28
PI7.Signal=FMC_D29
PI9.Signal=FMC_D30
RCC.HSE_VALUE=25000000
RCC.SYSCLKFreq_VALUE=180000000
RCC.SYSCLKSource=RCC_SYSCLKSOURCE_PLLCLK
board=fmc-test

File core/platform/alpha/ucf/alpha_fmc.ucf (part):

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#
NET  "gclk_pin"        LOC = "D17"  | IOSTANDARD = "LVCMOS33" ;
#
NET  "fmc_clk"         LOC = "W11"  | IOSTANDARD = "LVCMOS33" ;
NET  "fmc_ne1"         LOC = "V5"   | IOSTANDARD = "LVCMOS33" ;
NET  "fmc_noe"         LOC = "W16"  | IOSTANDARD = "LVCMOS33" ;
NET  "fmc_nwe"         LOC = "AA6"  | IOSTANDARD = "LVCMOS33" ;
NET  "fmc_nl"          LOC = "W17"  | IOSTANDARD = "LVCMOS33" ;
NET  "fmc_nwait"       LOC = "Y6"   | IOSTANDARD = "LVCMOS33" | SLEW = "FAST" | DRIVE = 8;
#
NET  "fmc_a<0>"        LOC = "Y17"  | IOSTANDARD = "LVCMOS33" ;
NET  "fmc_a<1>"        LOC = "AB16" | IOSTANDARD = "LVCMOS33" ;
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NET  "ct_noise"        LOC = "W19"  | IOSTANDARD = "LVCMOS33" ;

NET  "mkm_sclk"        LOC = "V3"   | IOSTANDARD = "LVCMOS33" ;
NET  "mkm_cs_n"        LOC = "W2"   | IOSTANDARD = "LVCMOS33" ;
NET  "mkm_di"          LOC = "W1"   | IOSTANDARD = "LVCMOS33" ; # MKM_FPGA_MOSI
NET  "mkm_do"          LOC = "Y1"   | IOSTANDARD = "LVCMOS33" ; # MKM_FPGA_MISO

#-------------------------------------------------------------------------------
# FMC Input Timing
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
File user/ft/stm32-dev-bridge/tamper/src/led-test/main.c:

#include <inttypes.h>
#include <avr/io.h>
//#include <util/delay.h>

#include "iotn828.h"

#define AVR_LED4 PORTA4  /* RED */
#define AVR_LED3 5  /* YELLOW */
#define AVR_LED2 6  /* GREEN */
#define AVR_LED1 7  /* BLUE */


void main() {
  int i;
  uint8_t j = 0;

  /* Enable PA4 output */
  //  DDRA |= (1 << AVR_LED4) | (1 << AVR_LED3) | (1 << AVR_LED2) | (1 << AVR_LED1);
  DDRA |= 0xf0;

  //PORTA = 0;
  while (1) {
    PORTA = (PORTA & 0x0f) | ((j++<<4) & 0xf0);
    //PORTA ^= (1 << AVR_LED1);
    //PORTA = j++;
    for (i = 0; i < 10000; i++) { ; }
    //_delay_ms (100);
  }
}

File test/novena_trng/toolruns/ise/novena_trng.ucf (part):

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# NET "EIM_WAIT" LOC = A7;
# NET "EIM_WAIT" IOSTANDARD = LVCMOS33;

# #NET "FPGA_DONE" LOC = V17;
# #NET "FPGA_DONE" IOSTANDARD = LVCMOS33;
# #NET "FPGA_HSWAPEN" LOC = D4;
# #NET "FPGA_HSWAPEN" IOSTANDARD = LVCMOS33;
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# NET "FPGA_LSPI_WP" LOC = C1;
# NET "FPGA_LSPI_WP" IOSTANDARD = LVCMOS33;

# #NET "FPGA_M0" LOC = T15;
# #NET "FPGA_M0" IOSTANDARD = LVCMOS33;
# #NET "FPGA_M1" LOC = N12;
# #NET "FPGA_M1" IOSTANDARD = LVCMOS33;

# #NET "FPGA_RESET_N" LOC = V2;
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
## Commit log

2018-10-22 Usage instructions for cloning submodules from CrypTech
2018-10-22 adding x25519 submodule
2018-10-22 modifying directory hierarchy
2018-10-22 updating folder hierarchy
2018-10-23 updating broken submodule paths to point at the correct repos
2018-10-25 removing scaffolding file

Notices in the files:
core/platform/alpha/ucf/alpha_fmc.ucf:
Copyright (c) 2016, NORDUnet A/S All rights reserved.
user/ft/alpha_to_kicad/rev03-KiCad/Cryptech Alpha.kicad_pcb:
Radically Open BSD License\r
